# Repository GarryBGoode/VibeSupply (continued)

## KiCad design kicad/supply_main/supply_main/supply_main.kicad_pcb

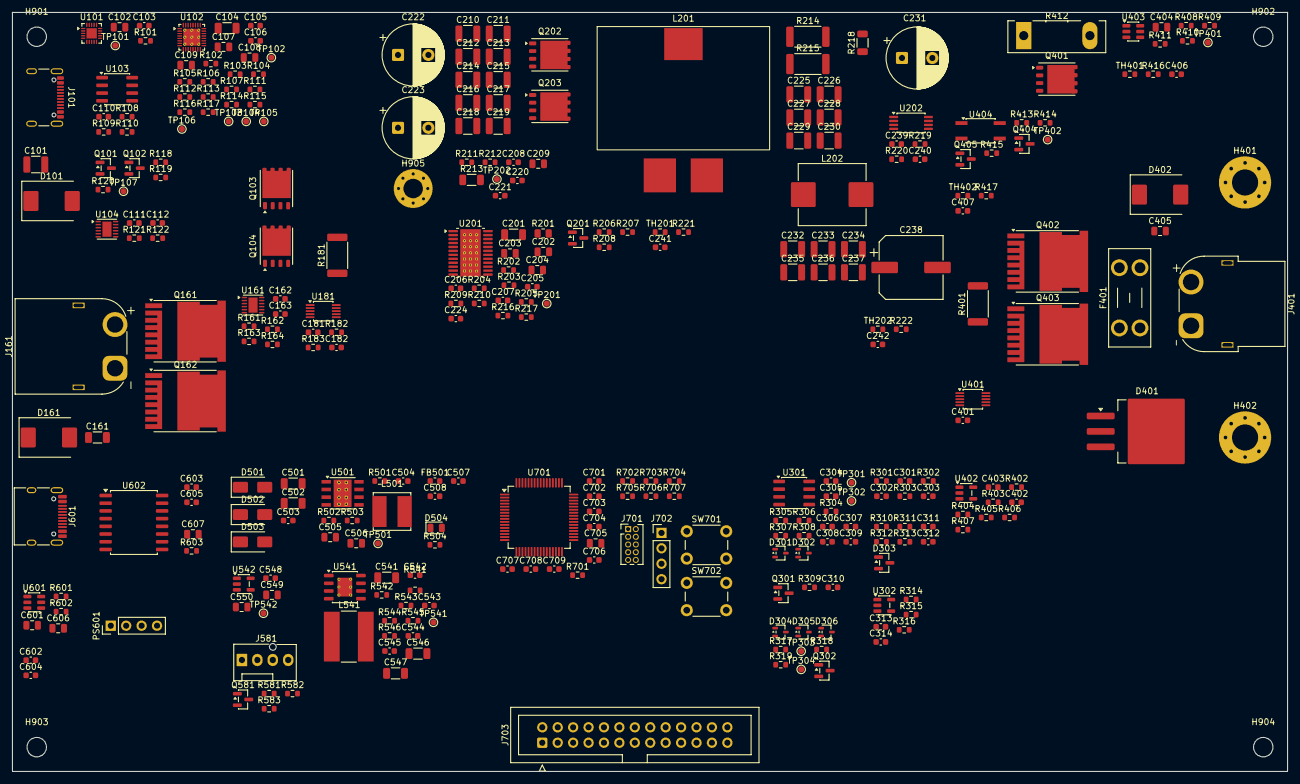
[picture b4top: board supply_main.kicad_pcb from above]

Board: 2 copper layers, 210.0 x 125.0 mm, 321 parts (0 on the bottom side), 176 nets, no tracks yet.

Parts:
C101, C210, C211, C212, C213, C214, C215, C216, C217, C218, C219, C225, C226, C227, C228, C229, C230, C232, C233, C234, C235, C236, C237: 4.7u; C_1210_3225Metric
C102, C405: 100n; C_0805_2012Metric
C103, C110, C111, C112, C162, C163, C181, C182, C208, C220, C221, C239, C241, C242, C301, C302, C304, C313, C314, C401, C403, C406, C407, C503, C504, C508, C542, C604, C605, C701, C702, C703, C704, C706, C708, C709: 100n; C_0603_1608Metric
C104: 4.7u; C_1206_3216Metric
C105, C106: 330p; C_0603_1608Metric
C107, C108, C109: 10u; C_0805_2012Metric
C161, C201: 1u; C_1206_3216Metric
C202, C203, C404, C549: 1u; C_0805_2012Metric
C204, C601, C606, C607, C705: 4.7u; C_0805_2012Metric
C205, C224, C240, C310, C402, C545: 1n; C_0603_1608Metric
C206, C307: 100p; C_0603_1608Metric
C207, C303, C311, C312, C548: 10n; C_0603_1608Metric
C209: 1n; C_0805_2012Metric
C222, C223: 100u 100V; CP_Radial_D10.0mm_P5.00mm
C231: 100u 63V; CP_Radial_D10.0mm_P5.00mm
C238: 100u 63V; CP_Elec_10x12.6
C305, C507, C602, C603, C707: 1u; C_0603_1608Metric
C306: 1.8n; C_0603_1608Metric
C308: 27n; C_0603_1608Metric
C309: 1.2n; C_0603_1608Metric
C501, C502, C541: 2.2u; C_1206_3216Metric
C505, C506: 22u; C_0805_2012Metric
C543: 2.2n; C_0603_1608Metric
C544: 3.3n; C_0603_1608Metric
C546, C547: 10u; C_1206_3216Metric
C550: 2.2u; C_0805_2012Metric
D101, D161, D402: SMCJ54A; D_SMC
D301, D302, D304, D305, D306: BAT54W; SOT-323_SC-70
D303: BAT54S; SOT-23
D401: MBRB40100CT; TO-263-3_TabPin2
D501, D502: SS110; D_SMA
D503: SS14; D_SMA
D504: green; LED_0805_2012Metric
F401: 30A 58V MINI; Fuseholder_Blade_Mini_Keystone_3568
FB501: 600R@100MHz; L_0603_1608Metric
H401: POST+; MountingHole_4.3mm_M4_Pad_Via
H402: POST-; MountingHole_4.3mm_M4_Pad_Via
H901, H902, H903, H904: M3; MountingHole_3.2mm_M3
H905: GND screw; MountingHole_3.2mm_M3_Pad_Via
J101: USB_C_Receptacle_USB2.0_16P; USB_C_Receptacle_GCT_USB4105-xx-A_16P_TopMnt_Horizontal
J161: XT60PW-M DC IN; AMASS_XT60PW-M_1x02_P7.20mm_Horizontal
J401: XT60PW-F OUT; AMASS_XT60PW-F_1x02_P7.20mm_Horizontal
J581: FAN 4-pin; FanPinHeader_1x04_P2.54mm_Vertical
J601: USB_C_Receptacle_USB2.0_16P; USB_C_Receptacle_HRO_TYPE-C-31-M-12
J701: SWD; PinHeader_2x05_P1.27mm_Vertical
J702: UART; PinHeader_1x04_P2.54mm_Vertical
J703: UI ribbon; IDC-Header_2x13_P2.54mm_Vertical
L201: 6.8uH SER2918H-682KL; L_Coilcraft_SER2918H
L202: 0.47uH; L_Changjiang_FXL1040
L501: 22uH; L_Bourns_SRN6045TA
L541: 68uH; L_Bourns-SRN8040_8x8.15mm
PS601: B0505S-1WR3; PinHeader_1x04_P2.54mm_Vertical
Q101, Q102, Q201, Q302, Q404, Q405, Q581: 2N7002; SOT-23
Q103, Q104, Q401: BSC040N10NS5; Infineon_PG-TDSON-8_6.15x5.15mm
Q161, Q162, Q402, Q403: IPT015N10N5; Infineon_PG-HSOF-8-1
Q202, Q203: ISC030N10NM6; Infineon_PG-TDSON-8_6.15x5.15mm
Q301: BC857; SOT-23
R101, R111, R112, R113, R114, R115, R116, R117, R118, R119, R120, R163, R206, R207, R208, R309, R317, R319, R408, R411, R415, R541, R543, R583: 100k; R_0603_1608Metric
R102, R103, R105: 0R; R_0603_1608Metric
R104, R106: DNP; R_0603_1608Metric
R107, R110, R122, R162, R183, R203, R210, R220, R221, R222, R307, R311, R313, R314, R316, R318, R403, R404, R414, R416, R417, R503, R545, R582, R701, R706, R707: 10k; R_0603_1608Metric
R108, R109, R219, R406, R702, R703: 4.7k; R_0603_1608Metric
R121, R161: 453k; R_0603_1608Metric
R164: 15k; R_0603_1608Metric
R181, R401: 1m; R_2512_6332Metric
R182, R310, R312, R402: 191k; R_0603_1608Metric
R201: 10; R_0805_2012Metric
R202: 61.9k; R_0603_1608Metric
R204: 330k; R_0603_1608Metric
R205: 71.5k; R_0603_1608Metric
R209, R546: 470k; R_0603_1608Metric
R211: 1; R_0603_1608Metric
R212: 0; R_0603_1608Metric
R213: 2.2; R_1206_3216Metric
R214, R215: 5m; R_2512_6332Metric
R216, R217: 10; R_0603_1608Metric
R218: 0.1; R_1206_3216Metric
R301, R302, R504, R581: 1k; R_0603_1608Metric
R303: 100; R_0603_1608Metric
R304: 95.3k; R_0603_1608Metric
R305: 5k; R_0603_1608Metric
R306: 35.7k; R_0603_1608Metric
R308: 2.37k; R_0603_1608Metric
R315: 12.7k; R_0603_1608Metric
R405, R407: 1M; R_0603_1608Metric
R409: 4.7; R_0603_1608Metric
R410: 2.2; R_0603_1608Metric
R412: 2R 100W LTO100; TO-247-2_Vertical
R413: 91; R_0603_1608Metric
R501: 66.5k; R_0603_1608Metric
R502: 23.2k; R_0603_1608Metric
R542: 22k; R_0603_1608Metric
R544: 90.9k; R_0603_1608Metric
R601, R602: 5.1k; R_0603_1608Metric
R603, R704, R705: 2.2k; R_0603_1608Metric
SW701: RESET; SW_PUSH_6mm
SW702: BOOT; SW_PUSH_6mm
TH201, TH202, TH401, TH402: 10k B3950; R_0603_1608Metric
TP101, TP102, TP103, TP104, TP105, TP106, TP107, TP201, TP202, TP301, TP302, TP303, TP304, TP401, TP402, TP501, TP541, TP542: TestPoint; TestPoint_Pad_D1.0mm
U101: TPD4S480; Texas_RUK0020B_WQFN-20-1EP_3x3mm_P0.4mm_EP1.7x1.7mm
U102: TPS26750; VQFN-32-1EP_4x4mm_P0.4mm_EP2.8x2.8mm_ThermalVias
U103: AT24C512C; SOIC-8_3.9x4.9mm_P1.27mm
U104, U161: LM74800; WSON-12-1EP_3x3mm_P0.5mm_EP1.5x2.5mm
U181, U401: INA228; TSSOP-10_3x3mm_P0.5mm
U201: LTC7801; HTSSOP-24-1EP_4.4x7.8mm_P0.65mm_EP3.4x7.8mm_Mask2.4x2.98mm_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
U202: INA240A2PW; TSSOP-8_4.4x3mm_P0.65mm
U301: ADA4522-2; SOIC-8_3.9x4.9mm_P1.27mm
U302, U402: LMV331; SOT-23-5
U403: UCC27511ADBV; SOT-23-6
U404: VOM1271; SO-4_4.4x3.6mm_P2.54mm
U501: LMR38010; TI_SO-PowerPAD-8_ThermalVias
U541: LM5164DDA; HSOP-8-1EP_3.9x4.9mm_P1.27mm_EP2.41x3.1mm_ThermalVias
U542: LP2985-5.0; SOT-23-5
U601: USBLC6-2SC6; SOT-23-6
U602: ADUM3160; SOIC-16W_7.5x10.3mm_P1.27mm
U701: STM32G474RETx; LQFP-64_10x10mm_P0.5mm

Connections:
+3V3: C107.1, C181.1, C401.1, C505.1, C506.1, C603.1, C605.1, C701.1, C702.1, C703.1, C704.1, C705.1, FB501.1, J701.1, J702.1, J703.1, J703.2, L501.2, R107.1, R208.1, R316.1, R413.1, R502.1, R504.1, R582.1, R702.1, R703.1, R704.1, R705.1, R706.1, R707.1, SW702.2, TP501.1, U102.32, U181.6, U401.2, U401.6, U602.12, U602.13, U602.14, U602.16, U701.1, U701.16, U701.32, U701.48, U701.64
+3V3A: C507.1, C508.1, C706.1, D303.2, FB501.2, R221.1, R222.1, R416.1, R417.1, U701.29
+5VA: C239.1, C304.1, C305.1, C314.1, C403.1, C550.1, R314.1, R405.1, R406.1, TP542.1, U202.5, U301.8, U302.5, U402.5, U542.5
+5V_ISO: C607.1, D503.2, PS601.4, R603.1
+12V_AUX: C202.1, C404.1, C544.2, C546.1, C547.1, C549.1, J581.2, L541.2, R544.1, TP541.1, U201.20, U403.1, U542.1, U542.3
AUX_BST: C543.1, U541.7
AUX_EN: R541.2, R542.1, U541.3
AUX_FB: C545.2, R544.2, R545.1, U541.5
AUX_RA: C544.1, C545.1, R546.2
AUX_SW: C543.2, L541.1, R546.1, U541.8
BOOT0: R701.1, SW702.1, U701.61
BUCK_BG: R212.1, U201.16
BUCK_BOOST: C208.1, U201.15
BUCK_DRVCC: C204.1, U201.17, U201.18
BUCK_INTVCC: C203.1, R202.1, R204.1, R206.1, U201.7, U201.11, U201.12, U201.22
BUCK_MODE: R206.2, R207.1, U201.5
BUCK_MODE_LO: Q201.3, R207.2
BUCK_OVLO: R209.2, R210.1, U201.23
BUCK_PSKIP: Q201.1, R208.2, U701.36
BUCK_RUN: R318.1, U701.34
BUCK_SENSE_N: C224.2, R217.2, U201.1
BUCK_SENSE_P: C224.1, R216.2, U201.24
BUCK_SS: C207.1, R204.2, U201.2
BUCK_TG: R211.1, U201.13
BUCK_VFB: C205.1, R202.2, R203.1, U201.3
BUCK_VINC: C201.1, R201.2, U201.19
BUZZER: J703.24, U701.21
CC_M: C309.1, R307.2, R308.1, U301.6
CC_OUT: D302.3, TP302.1, U301.7
CC_Z: C308.1, R308.2
CLAMP_CMP: R406.2, R407.1, U402.4, U403.6
CLAMP_DIS: R408.1, U403.5, U701.59
CLAMP_G: Q401.4, R409.2, R410.2, R411.1, TP401.1
CLAMP_R: Q401.5, R412.2
CLAMP_REF: R404.2, R405.2, U402.3
CLAMP_SNS: C402.1, R402.2, R403.1, R407.2, U402.1
CV_M: C307.1, R304.2, R305.1, R306.1, U301.2
CV_OUT: D301.3, TP301.1, U301.1
CV_Z: C306.1, R306.2
DACICL_F: C303.1, Q301.1, R303.2
DACI_F: C302.1, R302.2, U301.5
DACV_F: C301.1, R301.2, R404.1, U301.3
DAC_I: R302.1, U701.19
DAC_ICL: R303.1, U701.20
DAC_V: R301.1, U701.18
DCIN_EN: R163.2, R164.1, U161.6
DCIN_MID: C162.1, C163.2, Q161.3, Q162.3, R163.1, U161.3, U161.10, U161.12
DCIN_RAW: C161.1, D161.1, D502.2, J161.1, Q161.2, U161.2
ENC1_A: J703.15, U701.38
ENC1_B: J703.16, U701.39
ENC1_SW: J703.17, U701.5
ENC2_A: J703.19, U701.8
ENC2_B: J703.20, U701.9
ENC2_SW: J703.21, U701.6
FAN_PWM: Q581.1, R583.1, U701.30
FAN_PWM_PIN: J581.4, Q581.3
FAN_TACH: R581.2, R582.2, U701.33
FAN_TACH_PIN: J581.3, R581.1
FAULT: D304.3, D305.3, D306.3, Q302.1, Q405.1, R317.1, TP303.1, U701.4
GND: C101.2, C102.2, C103.2, C104.2, C105.2, C106.2, C107.2, C108.2, C109.2, C110.2, C111.2, C161.2, C162.2, C181.2, C182.2, C201.2, C202.2, C203.2, C204.2, C205.2, C206.2, C207.2, C209.2, C210.2, C211.2, C212.2, C213.2, C214.2, C215.2, C216.2, C217.2, C218.2, C219.2, C220.2, C221.2, C222.2, C223.2, C225.2, C226.2, C227.2, C228.2, C229.2, C230.2, C231.2, C232.2, C233.2, C234.2, C235.2, C236.2, C237.2, C238.2, C239.2, C240.2, C241.2, C242.2, C301.2, C302.2, C303.2, C304.2, C305.2, C310.2, C311.2, C312.2, C313.2, C314.2, C401.2, C402.2, C403.2, C404.2, C405.2, C406.2, C407.2, C501.2, C502.2, C503.2, C505.2, C506.2, C507.2, C508.2, C541.2, C542.2, C546.2, C547.2, C548.2, C549.2, C550.2, C603.2, C605.2, C607.2, C701.2, C702.2, C703.2, C704.2, C705.2, C706.2, C707.2, C708.2, C709.2, D101.2, D161.2, D303.1, D401.1, D401.3, D402.2, D504.1, H402.1, H905.1, J101.A1, J101.A12, J101.B1, J101.B12, J101.SH, J161.2, J401.2, J581.1, J701.3, J701.5, J701.9, J702.4, J703.3, J703.5, J703.11, J703.18, J703.25, J703.26, PS601.3, Q101.2, Q102.2, Q201.2, Q203.1, Q203.2, Q203.3, Q301.3, Q302.2, Q401.1, Q401.2, Q401.3, Q404.2, Q405.2, Q581.2, R102.2, R103.2, R105.2, R111.2, R112.2, R113.2, R114.2, R115.2, R116.2, R117.2, R122.2, R162.2, R164.2, R183.2, R203.2, R205.2, R210.2, R220.2, R305.2, R311.2, R313.2, R315.2, R317.2, R319.2, R403.2, R408.2, R411.2, R415.2, R501.2, R503.2, R542.2, R543.2, R545.2, R583.2, R603.2, R701.2, SW701.2, TH201.2, TH202.2, TH401.2, TH402.2, U101.8, U101.13, U101.18, U101.21, U102.11, U102.12, U102.14, U102.19, U102.33, U103.1, U103.2, U103.3, U103.4, U103.7, U104.7, U161.7, U181.1, U181.2, U181.7, U201.6, U201.8, U201.25, U202.1, U202.4, U202.6, U202.7, U301.4, U302.2, U401.1, U401.7, U402.2, U403.4, U501.1, U501.9, U541.1, U541.9, U542.2, U602.9, U602.15, U701.15, U701.27, U701.31, U701.47, U701.63
GND_ISO: C601.2, C602.2, C604.2, C606.2, J601.A1, J601.A12, J601.B1, J601.B12, J601.SH, PS601.1, R601.2, R602.2, U601.2, U602.2, U602.8
HW_OVP: D306.1, R316.2, U302.4
HW_OVP_REF: C313.1, R314.2, R315.1, U302.3
I2C1_SCL: R702.2, U102.9, U181.5, U401.5, U701.51
I2C1_SDA: R703.2, U102.8, U181.4, U401.4, U701.60
I2C2_SCL: J703.13, R704.2, U701.43
I2C2_SDA: J703.12, R705.2, U701.42
IL_AMP: R219.1, R307.1, U202.8
IL_SENSE+: L201.2, R214.1, R215.1, R216.1, U202.2
IL_SNS: C240.1, R219.2, R220.1, U701.24
INA_ALERT: R707.2, U181.3, U401.3, U701.3
ISO_UD+: J601.A6, J601.B6, U601.1, U601.6, U602.7
ISO_UD-: J601.A7, J601.B7, U601.3, U601.4, U602.6
ISO_VDD1: C602.1, C604.1, U602.3, U602.4, U602.5
ITH: C206.1, C306.2, C307.2, C308.2, C309.2, D301.1, D302.1, Q301.2, R309.1, TP201.1, U201.4
ITH_MON: C310.1, R309.2, U701.10
LCD_BL: J703.10, U701.57
LCD_CS: J703.7, U701.40
LCD_DC: J703.8, U701.41
LCD_MOSI: J703.6, U701.37
LCD_RST: J703.9, U701.54
LCD_SCK: J703.4, U701.35
LOGIC_IN: C501.1, C502.1, C503.1, D501.1, D502.1, D503.1, U501.2, U501.3
LOG_BOOT: C504.1, U501.7
LOG_FB: R502.2, R503.1, U501.5
LOG_SW: C504.2, L501.1, U501.8
unnamed: C102.1, U101.3
unnamed: R101.2, TP101.1, U101.9
unnamed: C109.1, U102.4
unnamed: R103.1, R104.2, U102.2
unnamed: R105.1, R106.2, U102.3
unnamed: R108.2, U102.15, U103.5
unnamed: R109.2, U102.16, U103.6
unnamed: R110.2, U102.17
unnamed: TP102.1, U101.16, U102.5
unnamed: R111.1, TP103.1, U102.6
unnamed: R112.1, TP104.1, U102.7
unnamed: R113.1, TP105.1, U102.18
unnamed: R114.1, U102.31
unnamed: R115.1, U102.30
unnamed: R116.1, U102.22
unnamed: R117.1, U102.23
unnamed: TP106.1, U102.13
unnamed: Q101.1, R118.2, U102.20
unnamed: Q103.4, U104.1
unnamed: Q104.4, U104.8
unnamed: C112.1, U104.11
unnamed: R121.1, U104.4
unnamed: R121.2, R122.1, U104.5
unnamed: Q161.1, U161.1
unnamed: Q162.1, U161.8
unnamed: C163.1, U161.11
unnamed: R161.1, U161.4
unnamed: R161.2, R162.1, U161.5
unnamed: R205.1, U201.10
unnamed: Q202.4, R211.2
unnamed: Q203.4, R212.2
unnamed: C209.1, R213.2
unnamed: R409.1, U403.2
unnamed: R410.1, U403.3
unnamed: R501.1, U501.4
unnamed: D504.2, R504.2
unnamed: R543.1, U541.4
unnamed: C548.1, U542.4
unnamed: J601.A5, R601.1
unnamed: J601.B5, R602.1
unnamed: J701.2, U701.49
unnamed: J701.4, U701.50
unnamed: J701.6, U701.56
NRST: C709.1, J701.10, SW701.1, U701.7
NTC_CLAMP: C406.1, R416.2, TH401.1, U701.23
NTC_FET: C241.1, R221.2, TH201.1, U701.11
NTC_IND: C242.1, R222.2, TH202.1, U701.22
NTC_OUTSW: C407.1, R417.2, TH402.1, U701.26
OCP_FLT: D305.1, U701.25
OE_BTN: J703.22, U701.55
OE_G: Q404.1, Q405.3, R414.2, R415.1
OE_LED_A: R413.2, U404.1
OE_LED_K: Q404.3, U404.2
OUT+: C405.1, D401.2, D402.1, F401.2, H401.1, J401.1, R312.1
OUTSW_G: Q402.1, Q403.1, TP402.1, U404.4
OUTSW_MID: Q402.2, Q403.2, U404.3
OUT_EN: R414.1, U701.58
OVP_FLT: D304.1, U701.12
PD_CC1: C105.1, U101.12, U102.24
PD_CC2: C106.1, U101.11, U102.25
PD_C_CC1: J101.A5, U101.4, U101.7
PD_C_CC2: J101.B5, U101.5, U101.6
PD_IRQ: R107.2, U102.10, U701.62
PD_LDO3V3: C103.1, C108.1, C110.1, R101.1, R104.1, R106.1, R108.1, R109.1, R110.1, R118.1, R119.1, R120.1, U101.10, U102.1, U103.8
PD_PP5V: R102.1, U102.28, U102.29
PD_PPE_N: Q101.3, Q102.1, R119.2
PD_SINK_EN: Q102.3, R120.2, TP107.1, U104.6
PWR_BTN: J703.23, U701.2
RUN: Q302.3, R318.2, R319.1, TP304.1, U201.21
SW: C208.2, L201.1, Q202.1, Q202.2, Q202.3, Q203.5, R213.1, TP202.1, U201.14
UART_RX: J702.3, U701.53
UART_TX: J702.2, U701.52
UI_INT: J703.14, R706.2, U701.44
USBIN_MID: C111.1, C112.2, Q103.5, Q104.5, U104.3, U104.10, U104.12
USB_DM: U602.11, U701.45
USB_DP: U602.10, U701.46
VBUS_LV: C104.1, U101.19, U102.26, U102.27
VBUS_PC: C601.1, C606.1, J601.A4, J601.A9, J601.B4, J601.B9, PS601.2, U601.5, U602.1
VBUS_RAW: C101.1, D101.1, D501.2, J101.A4, J101.A9, J101.B4, J101.B9, Q103.1, Q103.2, Q103.3, U101.20, U104.2
VC1: C225.1, C226.1, C227.1, C228.1, C229.1, C230.1, L202.1, R214.2, R215.2, R217.1, R218.1, U202.3
VC1_DAMP: C231.1, R218.2
VIN_BUS: Q104.1, Q104.2, Q104.3, Q162.2, R181.1, U104.9, U161.9, U181.10
VIN_PWR: C210.1, C211.1, C212.1, C213.1, C214.1, C215.1, C216.1, C217.1, C218.1, C219.1, C220.1, C221.1, C222.1, C223.1, C541.1, C542.1, Q202.5, R181.2, R182.1, R201.1, R209.1, R541.1, U181.8, U181.9, U541.2
VIN_SNS: C182.1, R182.2, R183.1, U701.17
VOUT_INT: C232.1, C233.1, C234.1, C235.1, C236.1, C237.1, C238.1, L202.2, R304.1, R310.1, R401.1, U401.10
VOUT_SH: Q402.3, R401.2, R402.1, R412.1, U401.8, U401.9
VOUT_SNS: C311.1, R310.2, R311.1, U302.1, U701.13
VREF+: C707.1, C708.1, U701.28
VTERM: F401.1, Q403.3
VTERM_SNS: C312.1, D303.3, R312.2, R313.1, U701.14

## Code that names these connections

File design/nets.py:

"""
Global nets shared between the schematic modules.

Naming: power rails are P<volt>..., signals are UPPER_SNAKE. Nets that cross to the MCU carry the
STM32 pin in the comment (pin map: design/mcu.py).
"""

from skidl import Net

# ---------------------------------------------------------------- grounds / rails
GND = Net("GND")
GND_ISO = Net("GND_ISO")          # PC side of the USB isolator (not connected to GND!)

VBUS_RAW = Net("VBUS_RAW")        # USB-C PD connector VBUS (5-28 V)
VBUS_S = Net("VBUS_S")            # after the AP33772S 5 mOhm current-sense resistor
DCIN_RAW = Net("DCIN_RAW")        # DC input wires (9-30 V, survives a 48 V battery)
VIN_BUS = Net("VIN_BUS")          # common bus after both ideal diodes
VIN_PWR = Net("VIN_PWR")          # after the input shunt = buck input
LOGIC_IN = Net("LOGIC_IN")        # diode-OR of VBUS_RAW / DCIN_RAW / P5V_ISO -> 3.3 V buck
P3V3 = Net("+3V3")
P3V3A = Net("+3V3A")              # MCU VDDA (ferrite-filtered)
P12V = Net("+12V_AUX")            # LM5164 aux rail: LTC7803 EXTVCC (must be >= 7 V), clamp gate driver, 5 V analog LDO, fan (DNP)
P5VA = Net("+5VA")                # analog 5 V: op-amps, INA240, comparators, AP33772S V5V (via diode)
VBUS_PC = Net("VBUS_PC")          # isolated side: PC USB VBUS
P5V_ISO = Net("+5V_ISO")          # B0505S output (our side)

# ---------------------------------------------------------------- power stage
ITH = Net("ITH")                  # LTC7803 ITH: pulled down by CV amp, CC amp, current clamp
RUN = Net("RUN")                  # LTC7803 RUN
VOUT_INT = Net("VOUT_INT")        # after post filter (CV sense point)
VOUT_SH = Net("VOUT_SH")          # after 1 mOhm output shunt (clamp attaches here)
VTERM = Net("VTERM")              # after output switch, before fuse
OUT_P = Net("OUT+")               # output terminal (after fuse)
IL_AMP = Net("IL_AMP")            # INA240A3 output, 0.2 V/A (inductor current) -> CC amp

# ---------------------------------------------------------------- MCU interface (pin in comment)
DAC_V = Net("DAC_V")              # PA4 DAC1_OUT1: Vout/10.19
DAC_I = Net("DAC_I")              # PA5 DAC1_OUT2: IL * 0.2 V/A
DAC_ICL = Net("DAC_ICL")          # PA6 DAC2_OUT1: ITH clamp PNP base
DACV_F = Net("DACV_F")            # filtered DAC_V (CV amp +, regen clamp reference)
VOUT_SNS = Net("VOUT_SNS")        # PA1 ADC1_IN2 / COMP1_INP: VOUT_INT / 12
OVP_FLT = Net("OVP_FLT")          # PA0 COMP1_OUT
VTERM_SNS = Net("VTERM_SNS")      # PA2 ADC1_IN3: terminal voltage / 12 (clamped)
VIN_SNS = Net("VIN_SNS")          # PA3 ADC1_IN4: VIN_PWR / 13
IL_SNS = Net("IL_SNS")            # PB0 ADC1_IN15 / COMP4_INP: IL_AMP * 0.68
OCP_FLT = Net("OCP_FLT")          # PB1 COMP4_OUT
ITH_MON = Net("ITH_MON")          # PC2 ADC1_IN8
NTC_FET = Net("NTC_FET")          # PC3 ADC1_IN9
NTC_IND = Net("NTC_IND")          # PC4 ADC2_IN5
NTC_CLAMP = Net("NTC_CLAMP")      # PC5 ADC2_IN11
NTC_OUTSW = Net("NTC_OUTSW")      # PB2 ADC2_IN12
BUCK_RUN = Net("BUCK_RUN")        # PB12 (high = run)
BUCK_PSKIP = Net("BUCK_PSKIP")    # PB14 (high/default = pulse-skip, low = forced continuous)
OUT_EN = Net("OUT_EN")            # PB5 (high = output switch on)
CLAMP_DIS = Net("CLAMP_DIS")      # PB6 (high = regen clamp disabled; default enabled)
FAULT = Net("FAULT")              # PC15 readback: OR of OVP_FLT, OCP_FLT, HW_OVP
I2C1_SCL = Net("I2C1_SCL")        # PA15 (power bus: AP33772S 0x52, INA228 0x40/0x41, opt. DAC80502)
I2C1_SDA = Net("I2C1_SDA")        # PB7
PD_IRQ = Net("PD_IRQ")            # PB9 (AP33772S INT, active high)
PD_SINK_EN = Net("PD_SINK_EN")    # PB3 (high = USB-C sink path on; was SWO)
DCIN_ON = Net("DCIN_ON")          # PB4 (high = DC input path allowed, still gated by its UVLO; added 2026-10-01)
INA_ALERT = Net("INA_ALERT")      # PC14
USB_DP = Net("USB_DP")            # PA12 (to ADuM3160 DD+)
USB_DM = Net("USB_DM")            # PA11 (to ADuM3160 DD-)

# UI board (ribbon)
I2C2_SCL = Net("I2C2_SCL")        # PA9
I2C2_SDA = Net("I2C2_SDA")        # PA8
UI_INT = Net("UI_INT")            # PA10
LCD_SCK = Net("LCD_SCK")          # PB13 SPI2_SCK
LCD_MOSI = Net("LCD_MOSI")        # PB15 SPI2_MOSI
LCD_CS = Net("LCD_CS")            # PC8
LCD_DC = Net("LCD_DC")            # PC9
LCD_RST = Net("LCD_RST")          # PC12
ENC1_A = Net("ENC1_A")            # PC6 TIM3_CH1
ENC1_B = Net("ENC1_B")            # PC7 TIM3_CH2
ENC1_SW = Net("ENC1_SW")          # UI board only: TCA9535 P05
ENC2_A = Net("ENC2_A")            # PC0 TIM1_CH1
ENC2_B = Net("ENC2_B")            # PC1 TIM1_CH2
ENC2_SW = Net("ENC2_SW")          # UI board only: TCA9535 P06
OE_BTN = Net("OE_BTN")            # PD2
LCD_BL = Net("LCD_BL")            # PB10 TIM2_CH3, display backlight PWM (2026-10-01; ribbon pin 18, was UI_SPARE on PC13)
BUZZER = Net("BUZZER")            # PA7 TIM17_CH1
UART_TX = Net("UART_TX")          # PC10 USART3_TX
UART_RX = Net("UART_RX")          # PC11 USART3_RX

from skidl.pin import pin_drives as _drv


def power_net(*nets):
    """Mark nets that are driven by regulators/connectors through passives, so ERC knows they are powered."""
    for n in nets:
        n.drive = _drv.POWER


power_net(GND, GND_ISO, VBUS_RAW, VBUS_S, DCIN_RAW, VIN_BUS, VIN_PWR, LOGIC_IN, P3V3, P3V3A,
          P12V, P5VA, VBUS_PC, P5V_ISO)
